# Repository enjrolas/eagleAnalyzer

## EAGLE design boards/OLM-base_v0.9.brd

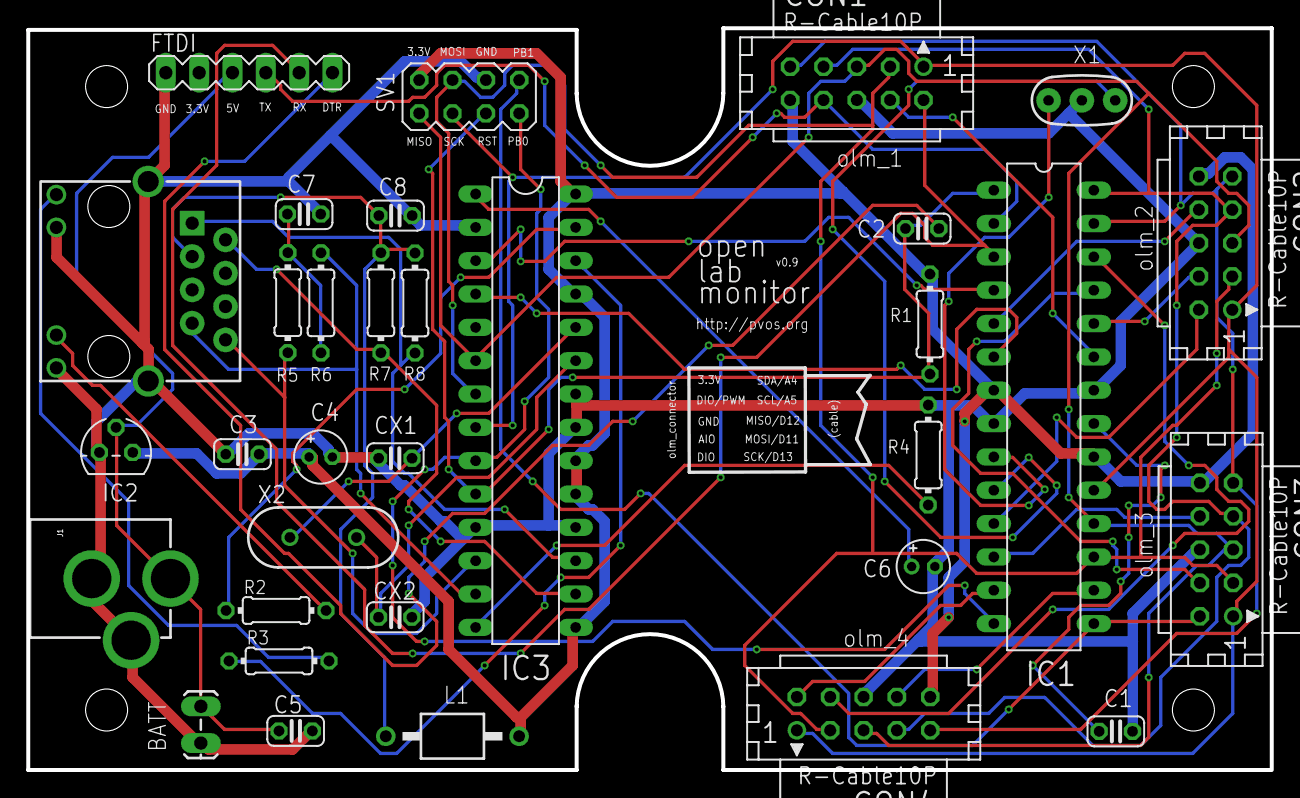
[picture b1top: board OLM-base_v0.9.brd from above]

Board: 2 copper layers, 94.7 x 56.5 mm, 33 parts (0 on the bottom side), 42 nets.

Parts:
C1, C2, C3, C5, C7, C8: 0.1µ; C025-024X044
C4: 10µ; E1,8-4
C6: 10u; E1,8-4
CON1, CON2, CON3, CON4: CON10L
CX1, CX2: 18p; C025-024X044
FTDI: FTDI; MA06-1
IC1: ATMEGA; DIL28-3
IC2: MCP1702-33; TO92
IC3: ENC28J60SP; DIL28-3
J1: POWER_JACKPTH; POWER_JACK_PTH
J2: MAGJACK
JP1: BATT; 1X02_LOCK_LONGPADS
L1: BL01RN1A
R1: 10k; 0204/7
R2, R3: 1K; 0204/7
R4: 2.32K; 0204/7
R5, R6, R7, R8: 49.9; 0204/7
SV1: SPI/ISP; MA04-2
X1: 16 MHz; RESONATOR-PTH
X2: 25MHz; HC49US

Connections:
A0: CON1.4, IC1.23
A1: CON2.4, IC1.24
A2: CON3.4, IC1.25
A3: CON4.4, IC1.26
D0/RX: CON1.8, FTDI.4, IC1.2
D1/TX: CON1.2, FTDI.5, IC1.3
D2: IC1.4, IC3.3
D3/PWM: CON2.8, IC1.5
D4: IC1.6, IC3.4
D5/PWM: CON2.2, IC1.11
D6/PWM: CON3.8, IC1.12
D7: CON4.2, IC1.13
D10/PWM: CON4.8, IC1.16
GND: C1.2, C3.2, C4.-, C5.2, C6.-, C7.1, C8.1, CON1.6, CON2.6, CON3.6, CON4.6, CX1.2, CX2.2, FTDI.1, IC1.8, IC1.22, IC2.1, IC3.2, IC3.11, IC3.18, IC3.21, IC3.22, J1.GND, J1.GNDBREAK, J2.10, J2.12, J2.M1, J2.M2, JP1.2, R4.2, SV1.6, X1.2
LEDA: J2.11, R2.2
LEDB: J2.9, R3.2
MISO/D12: CON1.5, CON2.5, CON3.5, CON4.5, IC1.18, IC3.6, SV1.1
MOSI/D11: CON1.3, CON2.3, CON3.3, CON4.3, IC1.17, IC3.7, SV1.4
unnamed: IC1.9, X1.1
unnamed: C1.1, IC1.21
unnamed: C2.2, FTDI.6
unnamed: IC1.10, X1.3
unnamed: IC3.27, R2.1
unnamed: IC3.26, R3.1
unnamed: C6.+, IC3.1
unnamed: IC3.14, R4.1
unnamed: CX1.1, IC3.24, X2.1
unnamed: CX2.1, IC3.23, X2.2
unnamed: C7.2, R5.2, R6.1
PB0/D8: IC1.14, IC3.9, SV1.7
PB1/D9/PWM: CON3.2, IC1.15, SV1.8
RD+: IC3.13, J2.7, R6.2
RD-: IC3.12, J2.8, R5.1
RESET: C2.1, IC1.1, IC3.10, R1.1, SV1.5
SCK/D13: CON1.1, CON2.1, CON3.1, CON4.1, IC1.19, IC3.8, SV1.3
SCL/A5: CON1.7, CON2.7, CON3.7, CON4.7, IC1.28
SDA/A4: CON1.9, CON2.9, CON3.9, CON4.9, IC1.27
TCT: C8.2, J2.3, L1.1, R7.2, R8.1
TD+: IC3.17, J2.1, R8.2
TD-: IC3.16, J2.2, R7.1
VCC: C3.1, C4.+, CON1.10, CON2.10, CON3.10, CON4.10, IC1.7, IC1.20, IC2.3, IC3.15, IC3.19, IC3.20, IC3.25, IC3.28, L1.2, R1.2, SV1.2
VIN: C5.1, FTDI.3, IC2.2, J1.PWR, JP1.1

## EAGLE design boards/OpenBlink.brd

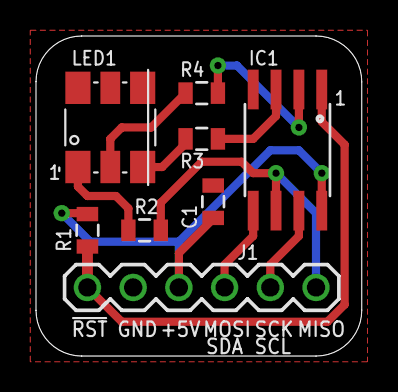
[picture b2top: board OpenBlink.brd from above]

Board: 2 copper layers, 18.1 x 17.8 mm, 9 parts (1 on the bottom side), 11 nets.

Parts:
C1: 100nF; 0805
IC1: ATtiny85; SO08-EIAJ
J1: Interface; 1X06
LED1: RGB LED; LED-RGB-5050
R1: 10kΩ; 0805
R2, R3: 100Ω; 0805
R4: 220Ω; 0805
SY: OSHW-LOGOS; OSHW-LOGO-S

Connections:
!RESET: IC1.1, J1.1, R1.1
+5V: C1.1, IC1.8, J1.3, R1.2
GND: C1.2, IC1.4, J1.2, LED1.BK, LED1.GK, LED1.RK
MISO: IC1.6, J1.6, R2.2
MOSI/SDA: IC1.5, J1.4
unnamed: IC1.2, R4.2
unnamed: IC1.3, R3.2
unnamed: LED1.RA, R4.1
unnamed: LED1.GA, R3.1
unnamed: LED1.BA, R2.1
SCK/SCL: IC1.7, J1.5

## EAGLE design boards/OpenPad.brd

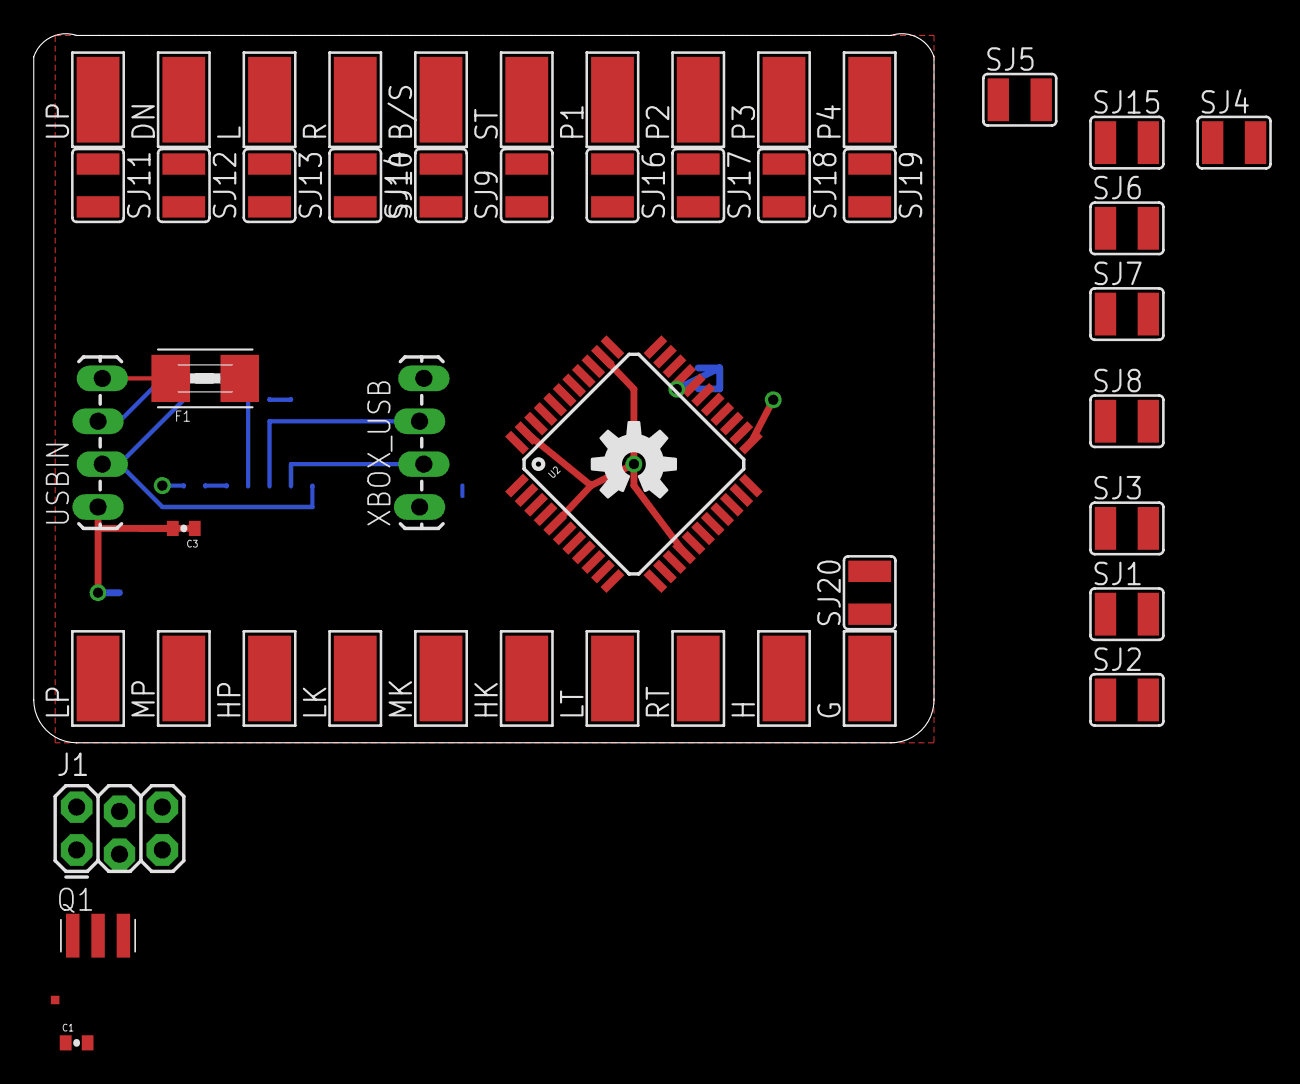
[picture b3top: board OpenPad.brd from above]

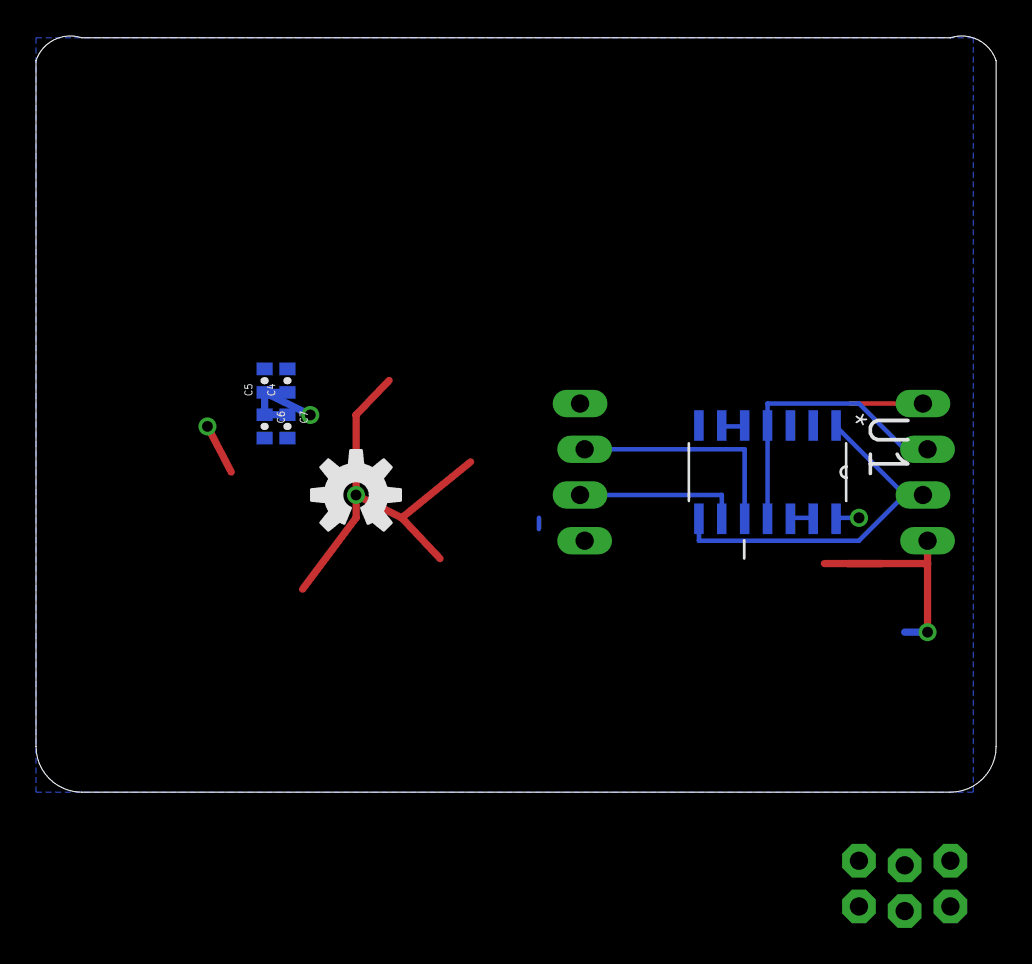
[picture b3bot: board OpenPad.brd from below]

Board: 2 copper layers, 53.3 x 42.0 mm, 56 parts (6 on the bottom side), 58 nets.

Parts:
B/S: BACK/SELECT; 5-2,5
C1: 1uF; 0402-CAP
C3, C4, C5, C6, C7: 0.1uF; 0402-CAP
DN: DOWN; 5-2,5
F1: 500mA; 1812
G: GND; 5-2,5
H: HOME; 5-2,5
HK: HK; 5-2,5
HP: HP; 5-2,5
J1: 2X3_LOCK
L: LEFT; 5-2,5
LK: LK; 5-2,5
LOGO1, LOGO2: OSHW-LOGOM; OSHW-LOGO-M
LP: LP; 5-2,5
LT: LT; 5-2,5
MK: MK; 5-2,5
MP: MP; 5-2,5
P1: P1; 5-2,5
P2: P2; 5-2,5
P3: P3; 5-2,5
P4: P4; 5-2,5
Q1: 16MHz; CSTCR6M
R: RIGHT; 5-2,5
RT: RT; 5-2,5
SJ1, SJ2, SJ3, SJ4, SJ5, SJ6, SJ7, SJ8, SJ9, SJ10, SJ11, SJ12, SJ13, SJ14, SJ15, SJ16, SJ17, SJ18, SJ19, SJ20: SJW
ST: START; 5-2,5
TP1: AREF; PAD.02X.02
U1: 4066D; SOIC127P600X175-14N
U2: ATMEGA32U4TQFP; SPARKFUN-DIGITALIC_TQFP44
UP: UP; 5-2,5
USBIN: 1X04_LOCK_LONGPADS
XBOX_USB: 1X04_LOCK_LONGPADS

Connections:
BACK/SELECT: SJ10.1, U2.36
D+: U1.4, U1.11, USBIN.3
D-: U1.1, U1.8, USBIN.2
DOWN: SJ12.2, U2.39
GND: C1.1, C3.2, C4.2, C5.2, C6.2, C7.2, J1.6, Q1.2, SJ20.2, U1.7, U2.5, U2.15, U2.23, U2.35, U2.43, USBIN.1, XBOX_USB.1
HK: SJ6.1, U2.22
HOME: SJ15.2, U2.27
HP: SJ3.1, U2.19
LEFT: SJ13.2, U2.38
LK: SJ4.1, U2.20
LP: SJ1.1, U2.8
LT: SJ7.1, U2.25
MISO: J1.1, U2.11
MK: SJ5.1, U2.21
MOSI: J1.4, U2.10
MP: SJ2.1, U2.18
unnamed: Q1.3, U2.16
unnamed: Q1.1, U2.17
unnamed: LP.1, SJ1.2
unnamed: F1.1, USBIN.4
unnamed: MP.1, SJ2.2
unnamed: HP.1, SJ3.2
unnamed: LK.1, SJ4.2
unnamed: MK.1, SJ5.2
unnamed: HK.1, SJ6.2
unnamed: LT.1, SJ7.2
unnamed: RT.1, SJ8.2
unnamed: SJ9.2, ST.1
unnamed: B/S.1, SJ10.2
unnamed: SJ11.1, UP.1
unnamed: DN.1, SJ12.1
unnamed: L.1, SJ13.1
unnamed: R.1, SJ14.1
unnamed: H.1, SJ15.1
unnamed: P2.1, SJ17.1
unnamed: P3.1, SJ18.1
unnamed: P4.1, SJ19.1
unnamed: G.1, SJ20.1
unnamed: P1.1, SJ16.1
unnamed: TP1.P$1, U2.42
unnamed: C1.2, U2.6
OPD+: U1.3, U2.4
OPD-: U1.2, U2.3
OP_EN: U1.5, U1.6, U2.41
P1: SJ16.2, U2.32
P2: SJ17.2, U2.31
P3: SJ18.2, U2.30
P4: SJ19.2, U2.29
RESET: J1.5, U2.13
RIGHT: SJ14.2, U2.37
RT: SJ8.1, U2.26
SCK: J1.3, U2.9
START: SJ9.1, U2.33
UP: SJ11.2, U2.40
VCC: C3.1, C4.1, C5.1, C6.1, C7.1, F1.2, J1.2, U1.14, U2.2, U2.7, U2.14, U2.24, U2.34, U2.44, XBOX_USB.4
XB_EN: U1.12, U1.13, U2.1
XD+: U1.10, XBOX_USB.3
XD-: U1.9, XBOX_USB.2

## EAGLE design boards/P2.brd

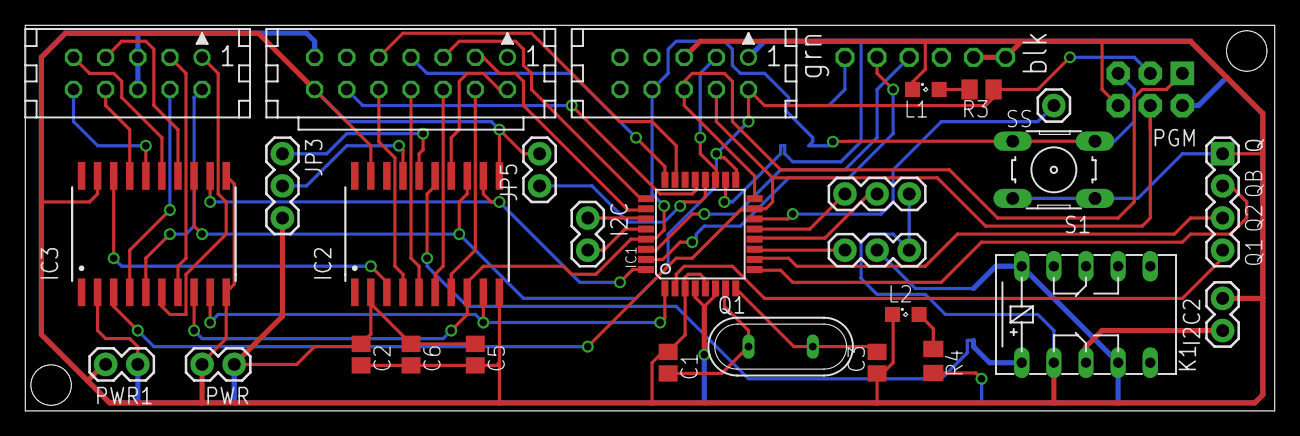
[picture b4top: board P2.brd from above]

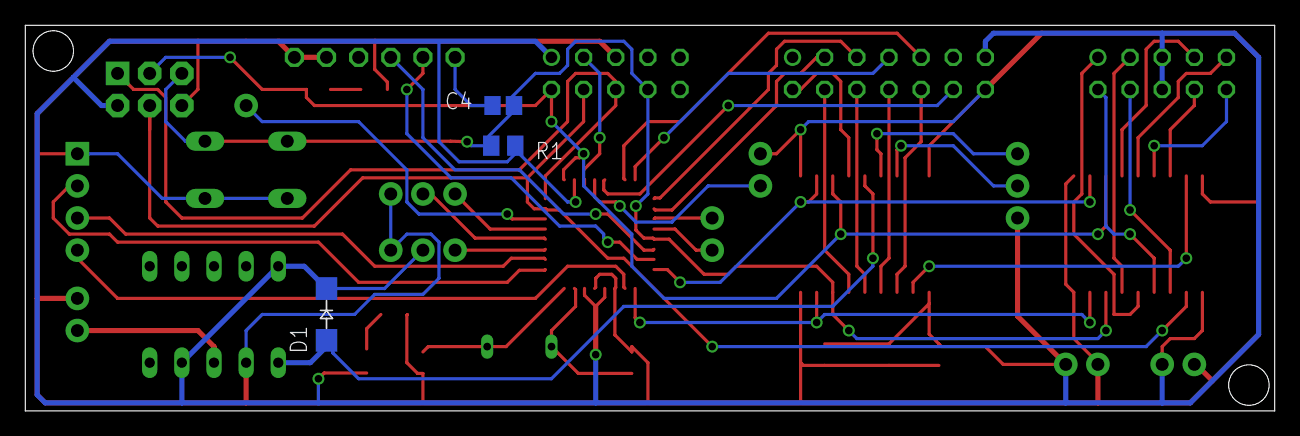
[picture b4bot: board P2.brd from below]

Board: 2 copper layers, 98.7 x 30.5 mm, 33 parts (3 on the bottom side), 49 nets.

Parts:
C1, C3: 22pF; C0805
C2, C4, C5: 0.1uF; C0805
C6: 1uF; C0805
CON1: Volume; CON10L
CON2: Autosense; CON14L
CON3: Noritake; CON10L
D1: GF1; SMA-DO214AC
I2C: scl sda; 1X02
I2C2: pwsw; 1X02
IC1: ATMEGA48/88/168-AU; TQFP32-08
IC2, IC3: TPIC6B595DW; SO20W
JP1: 1X06-CLEAN
JP2: pb1 pb0 gnd; 1X03
JP3: 1X03
JP4: ir; 1X03
JP5: aref; 1X02
K1: G6H2-100
L1, L2: SML0805
PGM: AVR_SPI_PRG_6NS; 2X3-NS
PWR, PWR1: - +; 1X02
Q: 1X04
Q1: 16MHz; QS
R1: 10K; M0805
R3, R4: 1k; M0805
S1: B3F-10XX
SS: M01PTH; 1X01

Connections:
+5V: C2.1, C5.1, C6.1, CON1.5, CON1.6, CON2.13, CON3.1, D1.K, IC1.4, IC1.6, IC1.18, IC2.2, IC3.2, JP3.3, JP4.2, K1.10, K1.S1, PGM.2, PWR.1, PWR1.1, R1.1, R4.2
ADC0: CON2.9, IC1.23
ADC1: CON2.7, IC1.24
ADC2: CON2.5, IC1.25
ADC3: CON2.3, IC1.26
AGND: CON2.12, IC1.21
G: IC1.1, IC2.9, IC3.9
GND: C1.1, C2.2, C3.1, C5.2, C6.2, CON2.14, CON3.5, I2C2.2, IC1.3, IC1.5, IC2.10, IC2.11, IC2.19, IC3.10, IC3.11, IC3.19, JP1.1, JP1.2, JP2.3, JP4.3, JP5.2, K1.O1, L1.C, L2.C, PGM.6, PWR.2, PWR1.2, Q.1, S1.1, S1.2
MISO: CON3.6, IC1.16, PGM.1
MOSI: CON3.4, IC1.15, IC3.3, PGM.4
unnamed: C1.2, IC1.7, Q1.1
unnamed: C3.2, IC1.8, Q1.2
unnamed: IC1.30, JP1.4
unnamed: IC1.31, JP1.5
unnamed: I2C2.1, K1.P1
unnamed: IC2.3, IC3.18
unnamed: I2C.1, IC1.27
unnamed: I2C.2, IC1.28
unnamed: IC1.13, JP2.1
unnamed: IC1.12, JP2.2
unnamed: IC2.16, JP3.1
unnamed: IC2.17, JP3.2
unnamed: IC1.20, JP5.1
unnamed: IC1.11, JP4.1
unnamed: L1.A, R3.1
unnamed: L2.A, R4.1
OUT0: CON1.4, IC3.4
OUT1: CON1.2, IC3.5
OUT2: CON1.1, IC3.6
OUT3: CON1.3, IC3.7
OUT4: CON1.7, IC3.14
OUT5: CON1.9, IC3.15
OUT6: CON1.10, IC3.16
OUT7: CON1.8, IC3.17
OUT8: CON2.10, IC2.4
OUT9: CON2.8, IC2.5
OUT10: CON2.6, IC2.6
OUT11: CON2.4, IC2.7
OUT12: CON2.2, IC2.14
OUT13: D1.A, IC2.15, K1.1
PC6: CON3.3, IC1.19
QE1: IC1.9, Q.2
QE2: IC1.10, Q.3
QEB: IC1.2, Q.4
RCK: IC1.32, IC2.12, IC3.12
RESET: C4.2, CON3.8, IC1.29, IC2.8, IC3.8, PGM.5, R1.2, S1.3, S1.4
RTS#: C4.1, JP1.6
SCK: CON3.2, IC1.17, IC2.13, IC3.13, PGM.3, R3.2
SS: IC1.14, SS.1

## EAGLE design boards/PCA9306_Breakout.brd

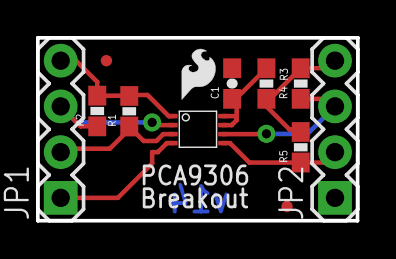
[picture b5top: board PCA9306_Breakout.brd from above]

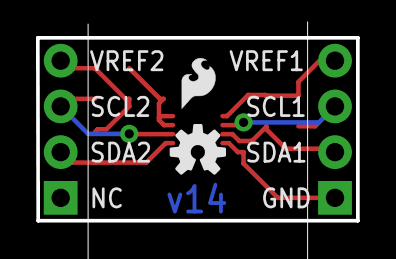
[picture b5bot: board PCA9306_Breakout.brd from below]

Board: 2 copper layers, 17.8 x 10.2 mm, 15 parts (2 on the bottom side), 8 nets.

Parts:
C1: 0.1uF; 0603-CAP
FRAME1: FRAME-LETTER; CREATIVE_COMMONS
JP1, JP2: 1X04
JP3, JP4: LOGO-SFESK; SFE-LOGO-FLAME
JP7, JP8: FIDUCIAL1X2.5; FIDUCIAL-1X2.5
LOGO1: OSHW-LOGOS; OSHW-LOGO-S
R1, R2, R4, R5: 1k; 0603-RES
R3: 200k; 0603-RES
U$1: PSOP-8

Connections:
GND: C1.2, JP1.1, U$1.4
SCL1: JP1.3, R2.1, U$1.2
SCL2: JP2.3, R4.1, U$1.6
SDA1: JP1.2, R1.1, U$1.3
SDA2: JP2.2, R5.1, U$1.5
VREF1: JP1.4, R1.2, R2.2, U$1.1
VREF2: C1.1, R3.1, U$1.7, U$1.8
VREF_2: JP2.4, R3.2, R4.2, R5.2

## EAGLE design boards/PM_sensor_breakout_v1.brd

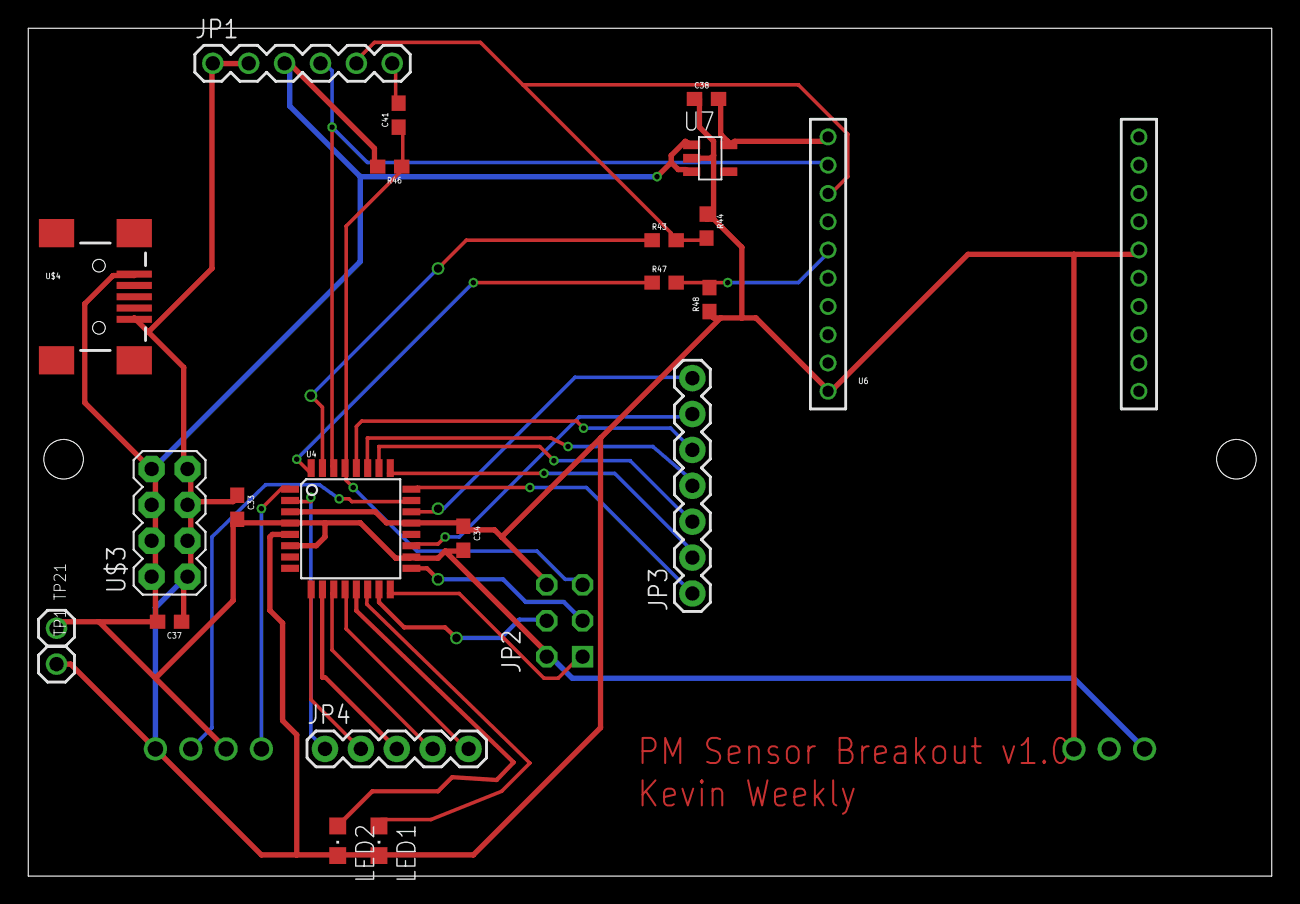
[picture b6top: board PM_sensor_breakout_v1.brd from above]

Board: 2 copper layers, 88.0 x 60.0 mm, 24 parts (1 on the bottom side), 29 nets.

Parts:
C33, C34, C41: .1u; 0603
C37, C38: 10u; 0603
J1: PPD60PV
JP1: 1X06
JP2: AVR_SPI_PRG_6NS; 2X3-NS
JP3: 1X07
JP4: 1X05
LED1, LED2: CHIPLED_0805
R43, R47: 4.7k; 0603
R44, R46, R48: 10k; 0603
TP1, TP21: TESTPOINT100MIL; TESTPOINT-100MIL
U4: ATMEGA168; TQFP32-08
U6: XBEE-1B1; XBEE-1
U7: TSOT23-5_LINEAR
U$3: M04X2; 2X4
U$4: USB-MINIB-5PIN; USB-MINIB

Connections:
3.3V: C38.2, U6.1, U7.5
5V: C33.2, C34.2, C37.2, J1.CN1_3, J1.CN2_3, JP1.3, JP2.2, R46.2, TP21.2, U4.4, U4.6, U4.18, U7.1, U7.3, U$3.2, U$3.4, U$3.6, U$3.8, U$4.VBUS
ANALOG: J1.CN1_2, U4.23
ATMEGA_TO_XB: JP1.5, R43.2, R44.2, U6.3
DIGITAL: J1.CN1_4, U4.1
GND: C33.1, C34.1, C37.1, C38.1, J1.CN1_1, J1.CN2_1, JP1.1, JP1.2, JP2.6, LED1.C, LED2.C, R44.1, R48.1, TP1.2, U4.3, U4.5, U4.21, U6.10, U6.16, U7.2, U$3.1, U$3.3, U$3.5, U$3.7, U$4.GND
MISO: JP2.1, U4.16
MOSI: JP2.4, U4.15
unnamed: LED2.A, U4.13
unnamed: JP3.1, U4.24
unnamed: LED1.A, U4.14
unnamed: JP3.2, U4.25
unnamed: JP3.3, U4.26
unnamed: JP3.4, U4.27
unnamed: JP3.5, U4.28
unnamed: JP3.6, U4.19
unnamed: JP3.7, U4.22
unnamed: JP4.1, U4.2
unnamed: JP4.2, U4.9
unnamed: JP4.3, U4.10
unnamed: JP4.4, U4.11
unnamed: JP4.5, U4.12
unnamed: R43.1, U4.31
unnamed: R47.1, U4.32
RST: C41.1, JP2.5, R46.1, U4.29
RTS#: C41.2, JP1.6
SCLK: JP2.3, U4.17
XB_RESET: R47.2, R48.2, U6.5
XB_TO_ATMEGA: JP1.4, U4.30, U6.2

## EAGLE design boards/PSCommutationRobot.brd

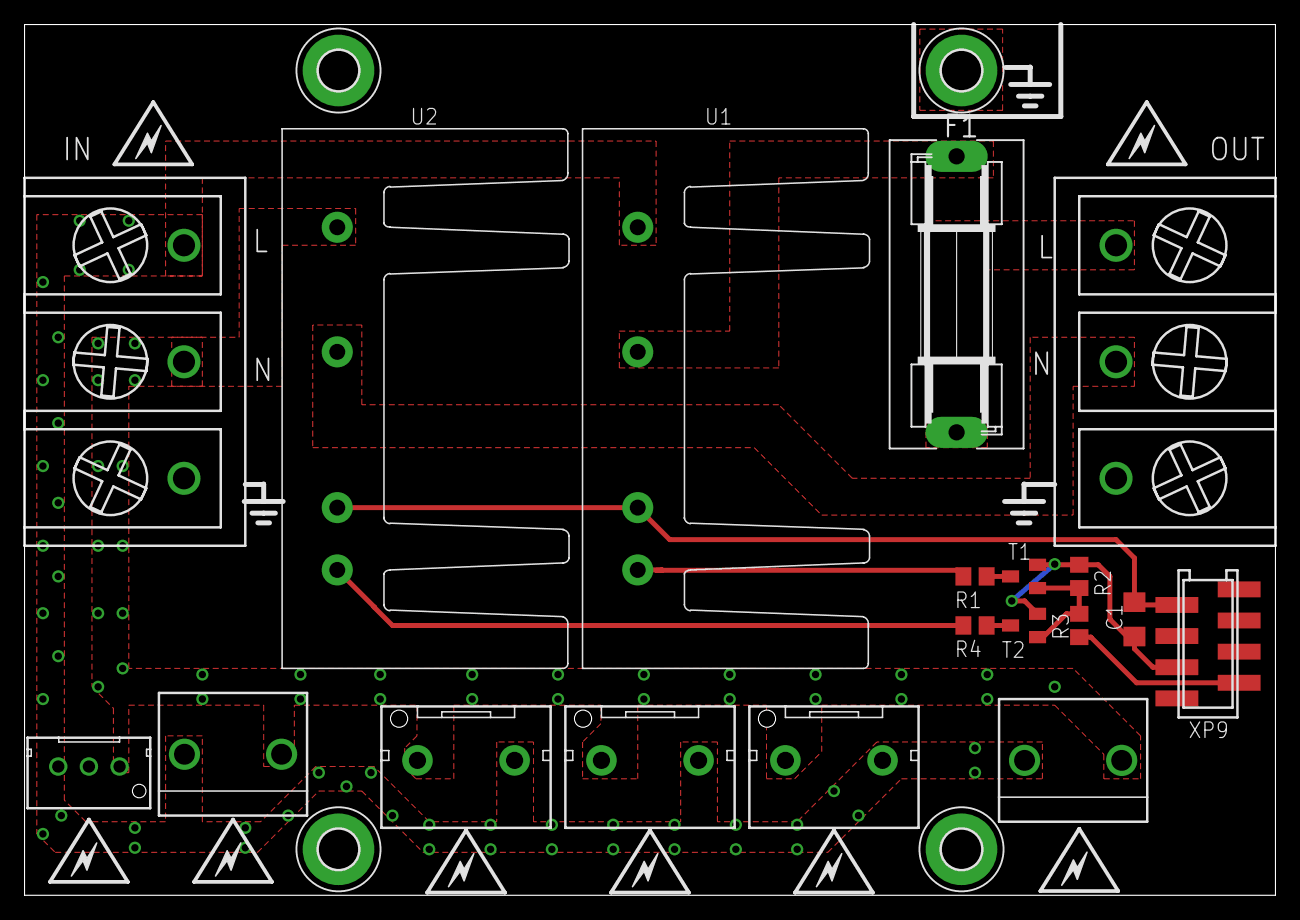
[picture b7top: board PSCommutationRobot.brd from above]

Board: 2 copper layers, 102.0 x 71.0 mm, 34 parts (0 on the bottom side), 14 nets.

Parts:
C1: 10uF; C1206
F1: FH-102; SH22,5A
H1, H2, H3, H4: MOUNT-PAD-ROUND3.3; 3,3-PAD
R1, R4: 220R 5%; R0805
R2: 10K 5%; R0805
R3: 1K 5%; R0805
T1, T2: BC847; SOT23-BEC
U1, U2: PF240D25; CRYDOM_PF240D25
U$1, U$2, U$3, U$4, U$5, U$6, U$7, U$8: ICON_BOLT-S
U$9, U$10, U$12: ICON_GND2
XP1: B3B-XH-A(M); JST_B3B-XH-AM
XP2, XP3: 09-65-2038; MOLEX_09-65-2038_WITHOUT_CENTRAL_PIN
XP4, XP5, XP6: B3P-VH-FB-B; JST_B3P-VH-FB-B_WITHOUT_CENTRAL_PIN
XP7, XP8: DT-49-B01W-03; DINKLE_DT-49-B01W-03
XP9: 7-188275-8; MMT-F-SMD-8

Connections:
ACL_IN: U1.1, XP1.3, XP2.1, XP3.1, XP4.3, XP5.3, XP6.3, XP7.3
ACL_OUT: F1.1, U1.2
ACN_IN: U2.1, XP1.1, XP2.2, XP3.2, XP4.1, XP5.1, XP6.1, XP7.2
ACN_OUT: U2.2, XP8.2
GND: H4.B3,3, XP7.1, XP8.3
GNDI: C1.2, R2.1, T1.E, T2.E, XP9.6
LVTTL_ON_!OFF: R3.1, XP9.7
unnamed: R1.1, T1.C
unnamed: R1.2, U1.4
unnamed: R2.2, R3.2, T1.B, T2.B
unnamed: R4.1, T2.C
unnamed: R4.2, U2.4
unnamed: F1.2, XP8.1
VCC: C1.1, U1.3, U2.3, XP9.2

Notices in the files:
parts and their libraries:
SparkFun-Connectors: Licensing: CC v3.0 Share-Alike You are welcome to use this library for commercial purposes.
SparkFun-Aesthetics: Released under the Creative Commons Attribution Share-Alike 3.0 License
SparkFun-Aesthetics: http://creativecommons.org/licenses/by-sa/3.0
